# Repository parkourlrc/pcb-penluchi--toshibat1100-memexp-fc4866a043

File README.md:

# toshibat1100-memexp
Toshiba T1100 laptop is the fist laptop from Toshiba and one of the first laptops in the world. It had 256KB memory included and there was possiblility to upgrade it to 512KB by adding a memory explansion board. This project represent a custom made memory expansion board based on original schematics. The schematic is taken by reverse engineering the original Toshiba T1100 memory expansion.

# TODO
Add BOM file

## Future plans
There is a plan to create a similar card based on memory chips that can be easily find nowdays. Stay tuned.

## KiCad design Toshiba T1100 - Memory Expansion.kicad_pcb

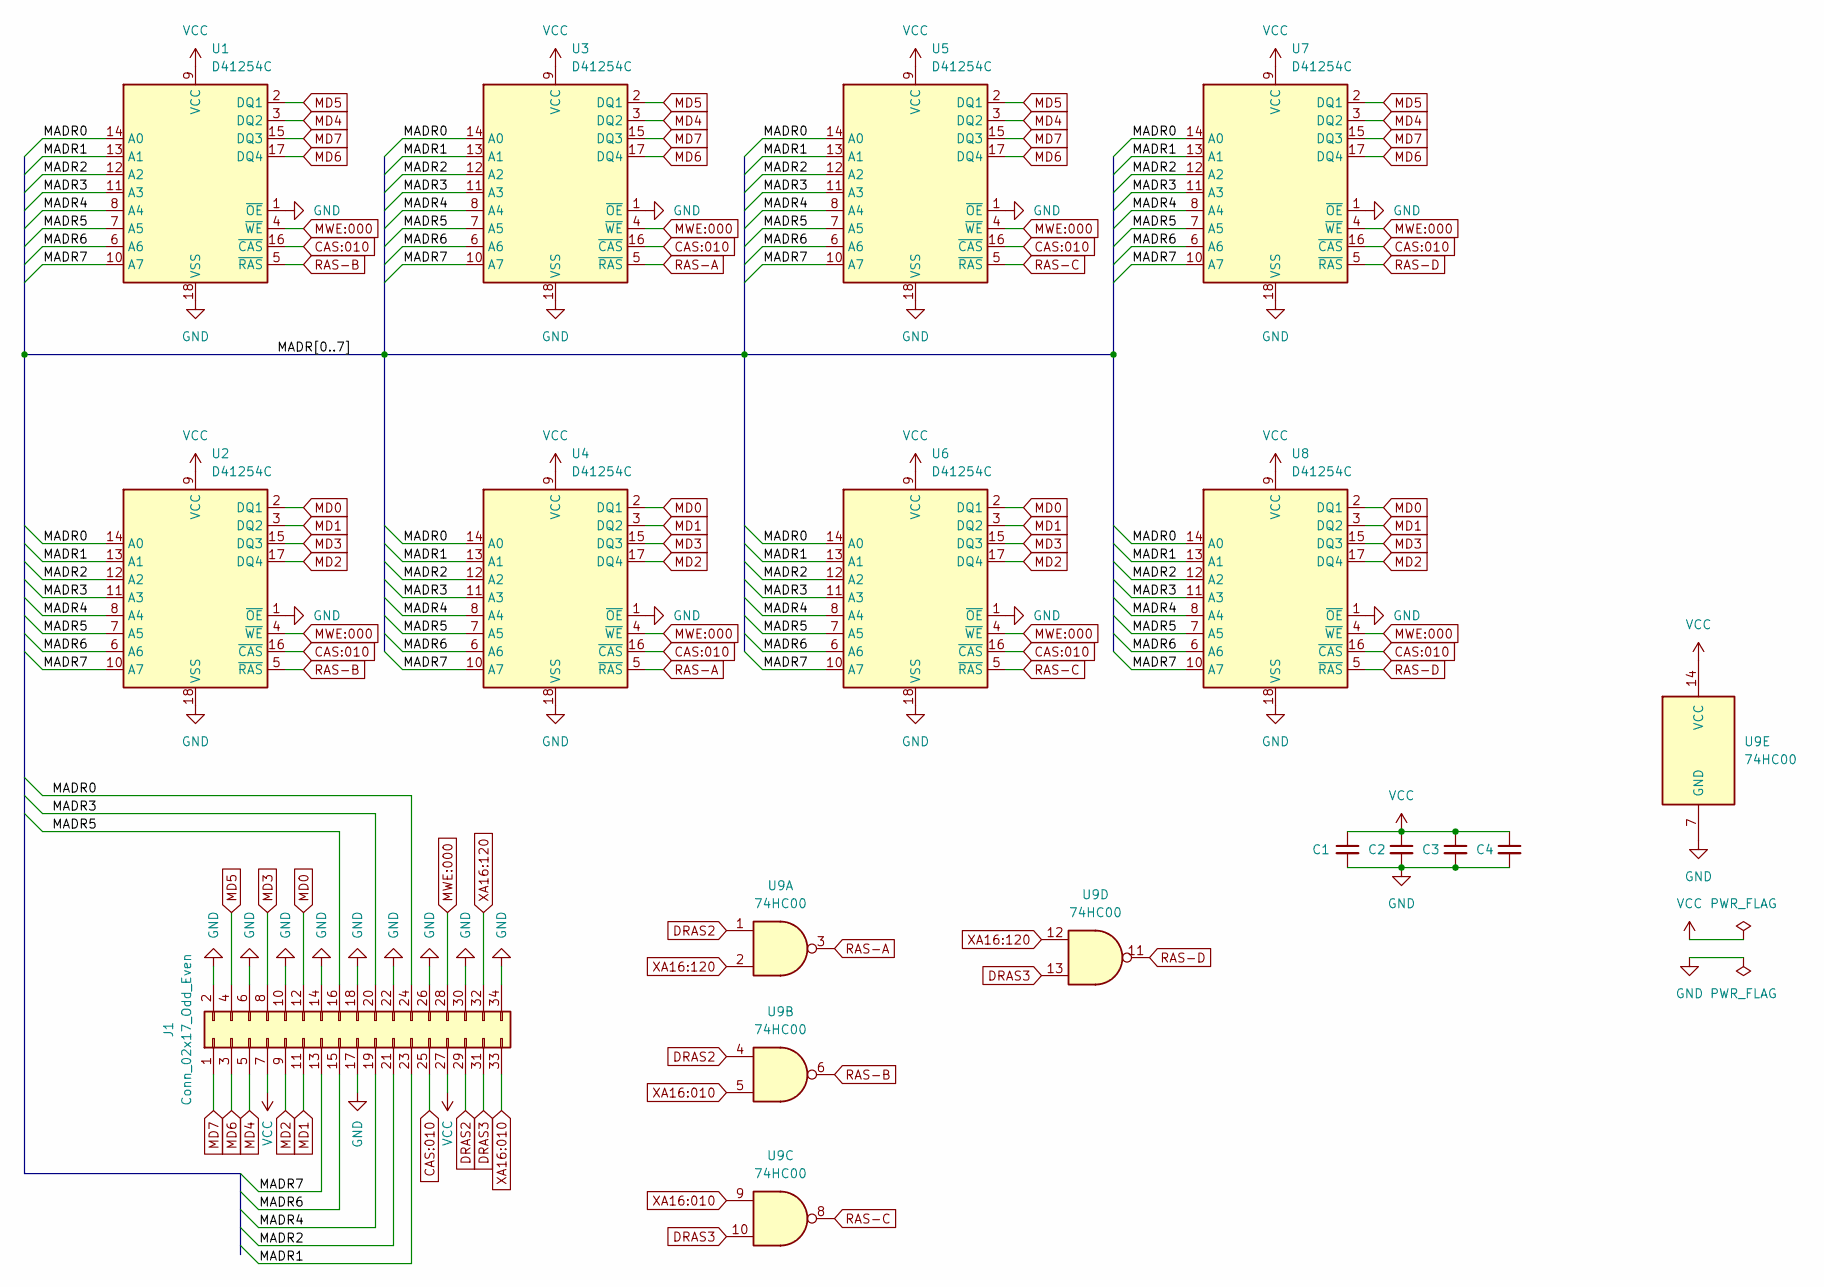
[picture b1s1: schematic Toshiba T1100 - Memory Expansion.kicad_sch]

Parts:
C1, C2, C3, C4: 1.5µF; C_Disc_D4.7mm_W2.5mm_P5.00mm
J1: Conn_02x17_Odd_Even; PinHeader_2x17_P2.54mm_Horizontal
U1, U2, U3, U4, U5, U6, U7, U8: D41254C; DIP-18_W7.62mm
U9: 74HC00; DIP-14_W7.62mm

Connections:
/MADR0: J1.24, U1.14 (A0), U2.14 (A0), U3.14 (A0), U4.14 (A0), U5.14 (A0), U6.14 (A0), U7.14 (A0), U8.14 (A0)
/MADR1: J1.23, U1.13 (A1), U2.13 (A1), U3.13 (A1), U4.13 (A1), U5.13 (A1), U6.13 (A1), U7.13 (A1), U8.13 (A1)
/MADR2: J1.21, U1.12 (A2), U2.12 (A2), U3.12 (A2), U4.12 (A2), U5.12 (A2), U6.12 (A2), U7.12 (A2), U8.12 (A2)
/MADR3: J1.20, U1.11 (A3), U2.11 (A3), U3.11 (A3), U4.11 (A3), U5.11 (A3), U6.11 (A3), U7.11 (A3), U8.11 (A3)
/MADR4: J1.19, U1.8 (A4), U2.8 (A4), U3.8 (A4), U4.8 (A4), U5.8 (A4), U6.8 (A4), U7.8 (A4), U8.8 (A4)
/MADR5: J1.16, U1.7 (A5), U2.7 (A5), U3.7 (A5), U4.7 (A5), U5.7 (A5), U6.7 (A5), U7.7 (A5), U8.7 (A5)
/MADR6: J1.15, U1.6 (A6), U2.6 (A6), U3.6 (A6), U4.6 (A6), U5.6 (A6), U6.6 (A6), U7.6 (A6), U8.6 (A6)
/MADR7: J1.13, U1.10 (A7), U2.10 (A7), U3.10 (A7), U4.10 (A7), U5.10 (A7), U6.10 (A7), U7.10 (A7), U8.10 (A7)
CAS:010: J1.25, U1.16 (~CAS), U2.16 (~CAS), U3.16 (~CAS), U4.16 (~CAS), U5.16 (~CAS), U6.16 (~CAS), U7.16 (~CAS), U8.16 (~CAS)
DRAS2: J1.29, U9.1, U9.4
DRAS3: J1.31, U9.10, U9.13
GND: C1.2, C2.2, C3.2, C4.2, J1.2, J1.6, J1.10, J1.14, J1.17, J1.18, J1.22, J1.26, J1.30, J1.34, U1.1 (~OE), U1.18 (VSS), U2.1 (~OE), U2.18 (VSS), U3.1 (~OE), U3.18 (VSS), U4.1 (~OE), U4.18 (VSS), U5.1 (~OE), U5.18 (VSS), U6.1 (~OE), U6.18 (VSS), U7.1 (~OE), U7.18 (VSS), U8.1 (~OE), U8.18 (VSS), U9.7 (GND)
MD0: J1.12, U2.2 (DQ1), U4.2 (DQ1), U6.2 (DQ1), U8.2 (DQ1)
MD1: J1.11, U2.3 (DQ2), U4.3 (DQ2), U6.3 (DQ2), U8.3 (DQ2)
MD2: J1.9, U2.17 (DQ4), U4.17 (DQ4), U6.17 (DQ4), U8.17 (DQ4)
MD3: J1.8, U2.15 (DQ3), U4.15 (DQ3), U6.15 (DQ3), U8.15 (DQ3)
MD4: J1.5, U1.3 (DQ2), U3.3 (DQ2), U5.3 (DQ2), U7.3 (DQ2)
MD5: J1.4, U1.2 (DQ1), U3.2 (DQ1), U5.2 (DQ1), U7.2 (DQ1)
MD6: J1.3, U1.17 (DQ4), U3.17 (DQ4), U5.17 (DQ4), U7.17 (DQ4)
MD7: J1.1, U1.15 (DQ3), U3.15 (DQ3), U5.15 (DQ3), U7.15 (DQ3)
MWE:000: J1.28, U1.4 (~WE), U2.4 (~WE), U3.4 (~WE), U4.4 (~WE), U5.4 (~WE), U6.4 (~WE), U7.4 (~WE), U8.4 (~WE)
RAS-A: U3.5 (~RAS), U4.5 (~RAS), U9.3
RAS-B: U1.5 (~RAS), U2.5 (~RAS), U9.6
RAS-C: U5.5 (~RAS), U6.5 (~RAS), U9.8
RAS-D: U7.5 (~RAS), U8.5 (~RAS), U9.11
VCC: C1.1, C2.1, C3.1, C4.1, J1.7, J1.27, U1.9 (VCC), U2.9 (VCC), U3.9 (VCC), U4.9 (VCC), U5.9 (VCC), U6.9 (VCC), U7.9 (VCC), U8.9 (VCC), U9.14 (VCC)
XA16:010: J1.33, U9.5, U9.9
XA16:120: J1.32, U9.2, U9.12

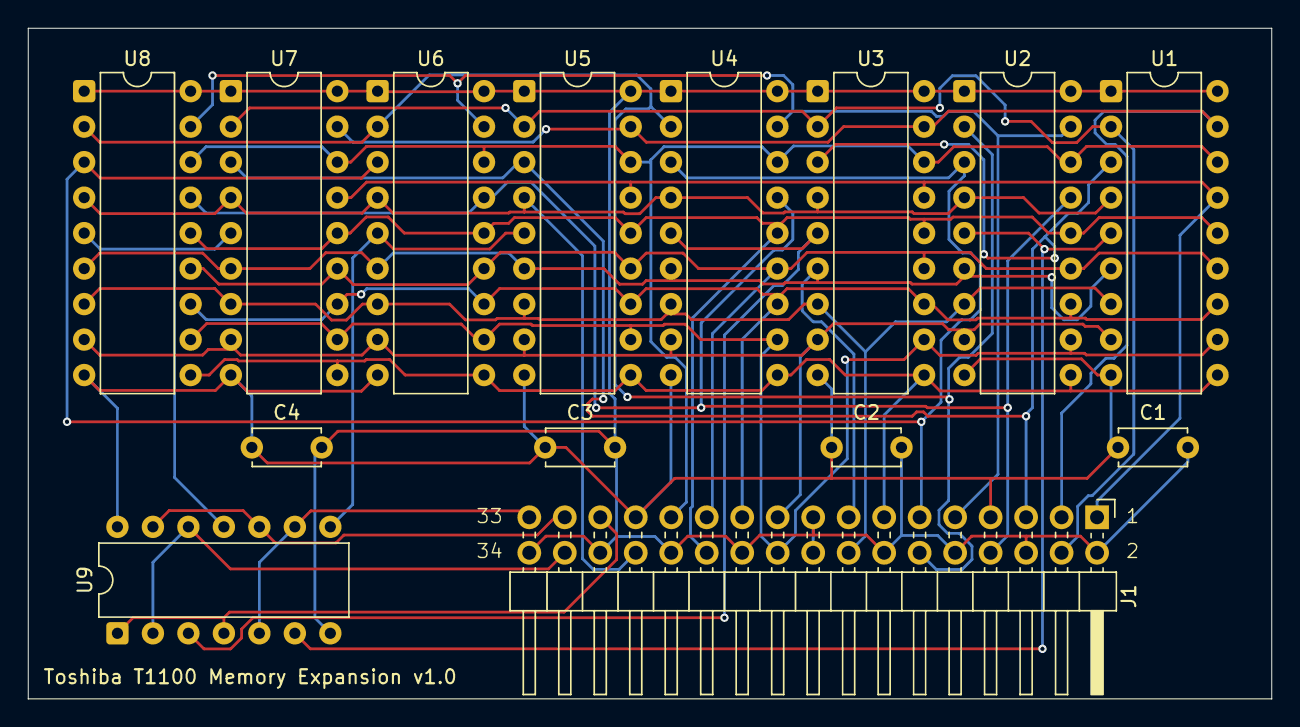
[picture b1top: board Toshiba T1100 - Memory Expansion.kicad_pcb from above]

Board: 2 copper layers, 89.0 x 48.0 mm, 14 parts (0 on the bottom side), 28 nets.

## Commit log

2025-07-11 Added Gerber files
2025-07-16 Smalll changes after PCBWay remarks.
2025-08-23 Made repo public
